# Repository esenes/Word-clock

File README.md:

# World-clock

Full raspberry pi zero 2 W setup process at the hackaday link
https://hackaday.io/project/198443-italian-word-clock

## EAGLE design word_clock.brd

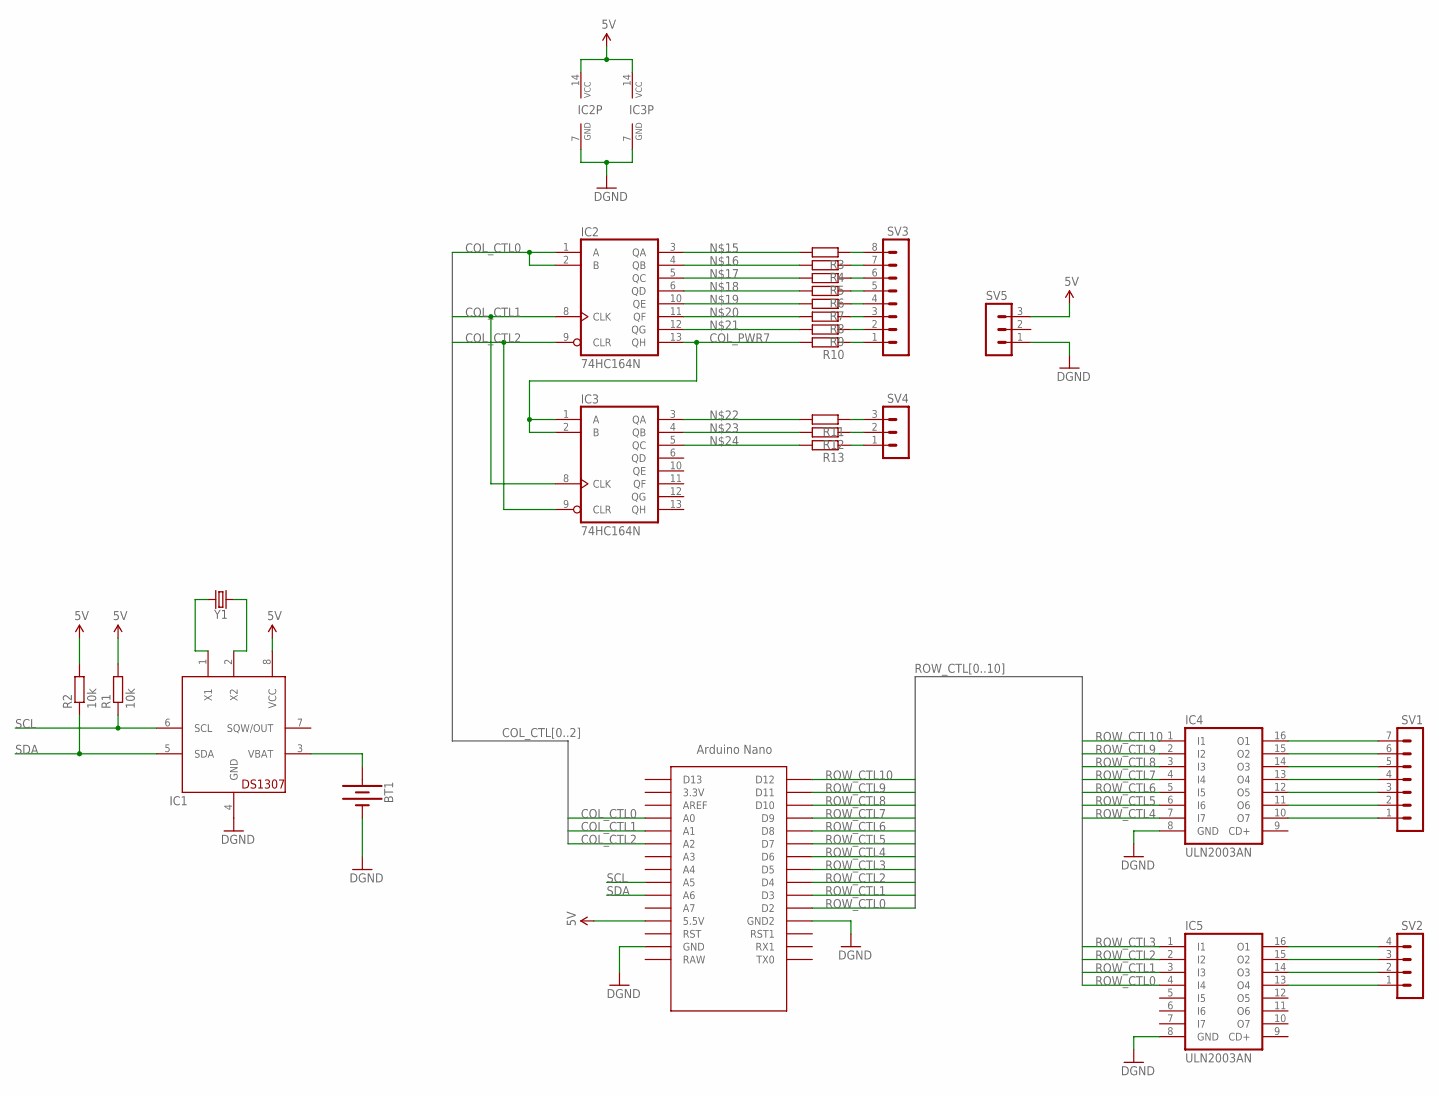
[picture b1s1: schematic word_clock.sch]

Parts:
BT1: BATTERY-20MM_PTH; BATTCOM_20MM_PTH
IC1: DS1307; DIL08
IC2, IC3: 74HC164N; DIL14
IC4, IC5: ULN2003AN; DIL16
R1, R2: 10k; 0207/10
R3, R4, R5, R6, R7, R8, R9, R10, R11, R12, R13: R-EU_0207/10; 0207/10
SV1: MA07-1
SV2: MA04-1
SV3: MA08-1
SV4, SV5: MA03-1
U$1: NANO_SHIELD
Y1: CRYSTALPTH-3X8; CRYSTAL-PTH-3X8-CYL

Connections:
5V: IC1.8 (VCC), IC2.14 (VCC), IC3.14 (VCC), R1.2, R2.2, SV5.3, U$1.5V (5.5V)
COL_CTL0: IC2.1 (A), IC2.2 (B), U$1.A0
COL_CTL1: IC2.8 (CLK), IC3.8 (CLK), U$1.A1
COL_CTL2: IC2.9 (CLR), IC3.9 (CLR), U$1.A2
COL_PWR7: IC2.13 (QH), IC3.1 (A), IC3.2 (B), R10.2
GND: BT1.2 (-), IC1.4 (GND), IC2.7 (GND), IC3.7 (GND), IC4.8 (GND), IC5.8 (GND), SV5.1, U$1.GND, U$1.GND1 (GND2)
unnamed: IC1.1 (X1), Y1.2
unnamed: BT1.1 (+), IC1.3 (VBAT)
unnamed: IC4.16 (O1), SV1.7
unnamed: IC4.15 (O2), SV1.6
unnamed: IC4.14 (O3), SV1.5
unnamed: IC4.13 (O4), SV1.4
unnamed: IC4.12 (O5), SV1.3
unnamed: IC4.11 (O6), SV1.2
unnamed: IC4.10 (O7), SV1.1
unnamed: IC5.16 (O1), SV2.4
unnamed: IC5.15 (O2), SV2.3
unnamed: IC5.14 (O3), SV2.2
unnamed: IC5.13 (O4), SV2.1
unnamed: IC1.2 (X2), Y1.1
unnamed: IC2.3 (QA), R3.2
unnamed: IC2.4 (QB), R4.2
unnamed: IC2.5 (QC), R5.2
unnamed: IC2.6 (QD), R6.2
unnamed: IC2.10 (QE), R7.2
unnamed: IC2.11 (QF), R8.2
unnamed: IC2.12 (QG), R9.2
unnamed: IC3.3 (QA), R11.2
unnamed: IC3.4 (QB), R12.2
unnamed: IC3.5 (QC), R13.2
unnamed: R11.1, SV4.3
unnamed: R12.1, SV4.2
unnamed: R13.1, SV4.1
unnamed: R10.1, SV3.1
unnamed: R9.1, SV3.2
unnamed: R8.1, SV3.3
unnamed: R7.1, SV3.4
unnamed: R6.1, SV3.5
unnamed: R5.1, SV3.6
unnamed: R4.1, SV3.7
unnamed: R3.1, SV3.8
ROW_CTL0: IC5.4 (I4), U$1.D2
ROW_CTL1: IC5.3 (I3), U$1.D3
ROW_CTL2: IC5.2 (I2), U$1.D4
ROW_CTL3: IC5.1 (I1), U$1.D5
ROW_CTL4: IC4.7 (I7), U$1.D6
ROW_CTL5: IC4.6 (I6), U$1.D7
ROW_CTL6: IC4.5 (I5), U$1.D8
ROW_CTL7: IC4.4 (I4), U$1.D9
ROW_CTL8: IC4.3 (I3), U$1.D10
ROW_CTL9: IC4.2 (I2), U$1.D11
ROW_CTL10: IC4.1 (I1), U$1.D12
SCL: IC1.6 (SCL), R1.1, U$1.A5
SDA: IC1.5 (SDA), R2.1, U$1.A6

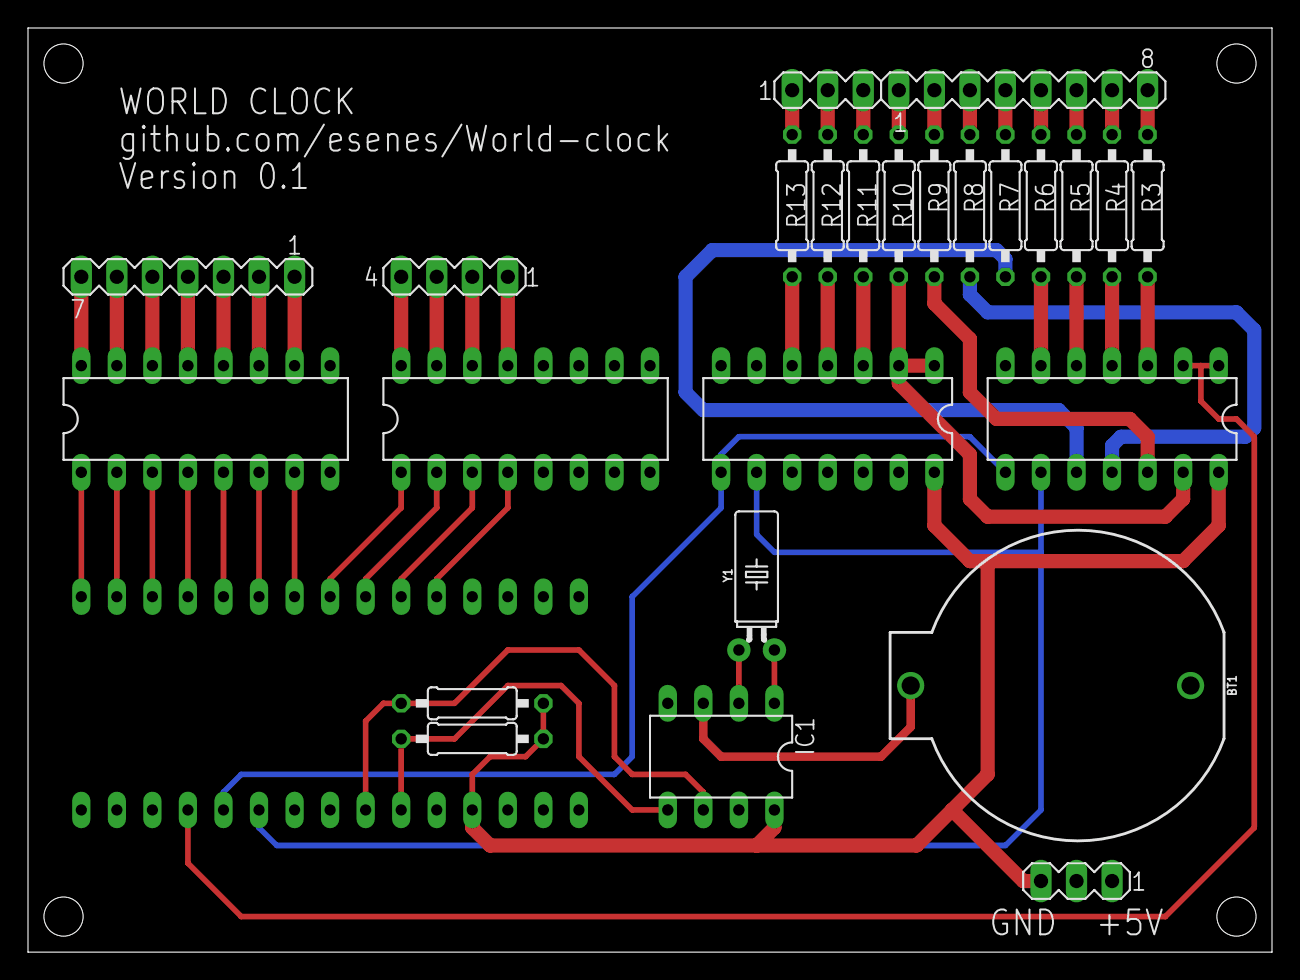
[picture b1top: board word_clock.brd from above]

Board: 2 copper layers, 88.9 x 66.0 mm, 26 parts (0 on the bottom side), 54 nets.

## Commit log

2019-04-14 eagle files v0.1
2019-04-26 fixed folder structure
2024-02-05 words for laser cut
2024-09-24 Update words

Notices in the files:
parts and their libraries:
SparkFun-Clocks: Licensing: Creative Commons ShareAlike 4.0 International - https://creativecommons.org/licenses/by-sa/4.0
